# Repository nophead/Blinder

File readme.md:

# Blinder

Tasmota roller blind open / close mechanism

<span></span>

---
## Table of Contents
1. [Parts list](#Parts_list)
1. [Pulley Assembly](#pulley_assembly)
1. [Switch Slide Assembly](#switch_slide_assembly)
1. [Rod Assembly](#rod_assembly)
1. [Retainer Assembly](#retainer_assembly)
1. [Idler Assembly](#idler_assembly)
1. [Base Assembly](#base_assembly)
1. [Motor Assembly](#motor_assembly)
1. [Bracket Assembly](#bracket_assembly)
1. [Blinder PCB Assembly](#blinder_PCB_assembly)
1. [Cover Assembly](#cover_assembly)
1. [Main Assembly](#main_assembly)

<span></span>
[Top](#TOP)

---

## Parts list
| <span style="writing-mode: vertical-rl; text-orientation: mixed;">Switch&nbsp;Slide</span> | <span style="writing-mode: vertical-rl; text-orientation: mixed;">Rod</span> | <span style="writing-mode: vertical-rl; text-orientation: mixed;">Base</span> | <span style="writing-mode: vertical-rl; text-orientation: mixed;">Motor</span> | <span style="writing-mode: vertical-rl; text-orientation: mixed;">Bracket</span> | <span style="writing-mode: vertical-rl; text-orientation: mixed;">Blinder&nbsp;PCB</span> | <span style="writing-mode: vertical-rl; text-orientation: mixed;">Cover</span> | <span style="writing-mode: vertical-rl; text-orientation: mixed;">Main</span> | <span style="writing-mode: vertical-rl; text-orientation: mixed;">TOTALS</span> |  |
|---:|---:|---:|---:|---:|---:|---:|---:|---:|:---|
|  |  |  |  |  |  |  |  | | **Vitamins** |
| &nbsp;&nbsp;.&nbsp; | &nbsp;&nbsp;.&nbsp; | &nbsp;&nbsp;2&nbsp; | &nbsp;&nbsp;.&nbsp; | &nbsp;&nbsp;.&nbsp; | &nbsp;&nbsp;.&nbsp; | &nbsp;&nbsp;.&nbsp; | &nbsp;&nbsp;.&nbsp; |  &nbsp;&nbsp;2&nbsp; | &nbsp;&nbsp; Ball bearing 686ZZ 6mm x 13mm x 5mm |
| &nbsp;&nbsp;.&nbsp; | &nbsp;&nbsp;.&nbsp; | &nbsp;&nbsp;.&nbsp; | &nbsp;&nbsp;.&nbsp; | &nbsp;&nbsp;.&nbsp; | &nbsp;&nbsp;1&nbsp; | &nbsp;&nbsp;.&nbsp; | &nbsp;&nbsp;.&nbsp; |  &nbsp;&nbsp;1&nbsp; | &nbsp;&nbsp; ESP-12F ESP8266 WiFi module |
| &nbsp;&nbsp;2&nbsp; | &nbsp;&nbsp;.&nbsp; | &nbsp;&nbsp;2&nbsp; | &nbsp;&nbsp;.&nbsp; | &nbsp;&nbsp;.&nbsp; | &nbsp;&nbsp;.&nbsp; | &nbsp;&nbsp;.&nbsp; | &nbsp;&nbsp;.&nbsp; |  &nbsp;&nbsp;4&nbsp; | &nbsp;&nbsp; Heatfit insert M2 x 4mm |
| &nbsp;&nbsp;.&nbsp; | &nbsp;&nbsp;.&nbsp; | &nbsp;&nbsp;10&nbsp; | &nbsp;&nbsp;1&nbsp; | &nbsp;&nbsp;.&nbsp; | &nbsp;&nbsp;.&nbsp; | &nbsp;&nbsp;.&nbsp; | &nbsp;&nbsp;.&nbsp; |  &nbsp;&nbsp;11&nbsp; | &nbsp;&nbsp; Heatfit insert M3 x 3mm |
| &nbsp;&nbsp;.&nbsp; | &nbsp;&nbsp;.&nbsp; | &nbsp;&nbsp;.&nbsp; | &nbsp;&nbsp;.&nbsp; | &nbsp;&nbsp;.&nbsp; | &nbsp;&nbsp;1&nbsp; | &nbsp;&nbsp;.&nbsp; | &nbsp;&nbsp;.&nbsp; |  &nbsp;&nbsp;1&nbsp; | &nbsp;&nbsp; JST PH connector 2 way |
| &nbsp;&nbsp;.&nbsp; | &nbsp;&nbsp;.&nbsp; | &nbsp;&nbsp;.&nbsp; | &nbsp;&nbsp;.&nbsp; | &nbsp;&nbsp;.&nbsp; | &nbsp;&nbsp;2&nbsp; | &nbsp;&nbsp;.&nbsp; | &nbsp;&nbsp;.&nbsp; |  &nbsp;&nbsp;2&nbsp; | &nbsp;&nbsp; JST PH connector 3 way |
| &nbsp;&nbsp;.&nbsp; | &nbsp;&nbsp;.&nbsp; | &nbsp;&nbsp;.&nbsp; | &nbsp;&nbsp;.&nbsp; | &nbsp;&nbsp;.&nbsp; | &nbsp;&nbsp;1&nbsp; | &nbsp;&nbsp;.&nbsp; | &nbsp;&nbsp;.&nbsp; |  &nbsp;&nbsp;1&nbsp; | &nbsp;&nbsp; LED 3 mm green |
| &nbsp;&nbsp;.&nbsp; | &nbsp;&nbsp;.&nbsp; | &nbsp;&nbsp;.&nbsp; | &nbsp;&nbsp;.&nbsp; | &nbsp;&nbsp;.&nbsp; | &nbsp;&nbsp;1&nbsp; | &nbsp;&nbsp;.&nbsp; | &nbsp;&nbsp;.&nbsp; |  &nbsp;&nbsp;1&nbsp; | &nbsp;&nbsp; MULTIWATT11 L6203 |
| &nbsp;&nbsp;1&nbsp; | &nbsp;&nbsp;.&nbsp; | &nbsp;&nbsp;1&nbsp; | &nbsp;&nbsp;.&nbsp; | &nbsp;&nbsp;.&nbsp; | &nbsp;&nbsp;.&nbsp; | &nbsp;&nbsp;.&nbsp; | &nbsp;&nbsp;.&nbsp; |  &nbsp;&nbsp;2&nbsp; | &nbsp;&nbsp; Microswitch DM1-00P-110-3 |
| &nbsp;&nbsp;.&nbsp; | &nbsp;&nbsp;.&nbsp; | &nbsp;&nbsp;.&nbsp; | &nbsp;&nbsp;.&nbsp; | &nbsp;&nbsp;.&nbsp; | &nbsp;&nbsp;1&nbsp; | &nbsp;&nbsp;.&nbsp; | &nbsp;&nbsp;.&nbsp; |  &nbsp;&nbsp;1&nbsp; | &nbsp;&nbsp; Molex KK header 2 way |
| &nbsp;&nbsp;.&nbsp; | &nbsp;&nbsp;.&nbsp; | &nbsp;&nbsp;.&nbsp; | &nbsp;&nbsp;.&nbsp; | &nbsp;&nbsp;.&nbsp; | &nbsp;&nbsp;1&nbsp; | &nbsp;&nbsp;.&nbsp; | &nbsp;&nbsp;.&nbsp; |  &nbsp;&nbsp;1&nbsp; | &nbsp;&nbsp; Molex KK housing 2 way |
| &nbsp;&nbsp;.&nbsp; | &nbsp;&nbsp;.&nbsp; | &nbsp;&nbsp;.&nbsp; | &nbsp;&nbsp;.&nbsp; | &nbsp;&nbsp;.&nbsp; | &nbsp;&nbsp;.&nbsp; | &nbsp;&nbsp;1&nbsp; | &nbsp;&nbsp;.&nbsp; |  &nbsp;&nbsp;1&nbsp; | &nbsp;&nbsp; Nut M3 x 2.4mm nyloc |
| &nbsp;&nbsp;.&nbsp; | &nbsp;&nbsp;.&nbsp; | &nbsp;&nbsp;1&nbsp; | &nbsp;&nbsp;.&nbsp; | &nbsp;&nbsp;.&nbsp; | &nbsp;&nbsp;.&nbsp; | &nbsp;&nbsp;.&nbsp; | &nbsp;&nbsp;.&nbsp; |  &nbsp;&nbsp;1&nbsp; | &nbsp;&nbsp; Nut M8 x 6.5mm brass |
| &nbsp;&nbsp;.&nbsp; | &nbsp;&nbsp;.&nbsp; | &nbsp;&nbsp;.&nbsp; | &nbsp;&nbsp;.&nbsp; | &nbsp;&nbsp;.&nbsp; | &nbsp;&nbsp;1&nbsp; | &nbsp;&nbsp;.&nbsp; | &nbsp;&nbsp;.&nbsp; |  &nbsp;&nbsp;1&nbsp; | &nbsp;&nbsp; PCB Blinder |
| &nbsp;&nbsp;.&nbsp; | &nbsp;&nbsp;.&nbsp; | &nbsp;&nbsp;.&nbsp; | &nbsp;&nbsp;.&nbsp; | &nbsp;&nbsp;.&nbsp; | &nbsp;&nbsp;2&nbsp; | &nbsp;&nbsp;.&nbsp; | &nbsp;&nbsp;.&nbsp; |  &nbsp;&nbsp;2&nbsp; | &nbsp;&nbsp; SMD capacitor 0805 100n |
| &nbsp;&nbsp;.&nbsp; | &nbsp;&nbsp;.&nbsp; | &nbsp;&nbsp;.&nbsp; | &nbsp;&nbsp;.&nbsp; | &nbsp;&nbsp;.&nbsp; | &nbsp;&nbsp;2&nbsp; | &nbsp;&nbsp;.&nbsp; | &nbsp;&nbsp;.&nbsp; |  &nbsp;&nbsp;2&nbsp; | &nbsp;&nbsp; SMD capacitor 0805 15n |
| &nbsp;&nbsp;.&nbsp; | &nbsp;&nbsp;.&nbsp; | &nbsp;&nbsp;.&nbsp; | &nbsp;&nbsp;.&nbsp; | &nbsp;&nbsp;.&nbsp; | &nbsp;&nbsp;1&nbsp; | &nbsp;&nbsp;.&nbsp; | &nbsp;&nbsp;.&nbsp; |  &nbsp;&nbsp;1&nbsp; | &nbsp;&nbsp; SMD capacitor 0805 220n |
| &nbsp;&nbsp;.&nbsp; | &nbsp;&nbsp;.&nbsp; | &nbsp;&nbsp;.&nbsp; | &nbsp;&nbsp;.&nbsp; | &nbsp;&nbsp;.&nbsp; | &nbsp;&nbsp;5&nbsp; | &nbsp;&nbsp;.&nbsp; | &nbsp;&nbsp;.&nbsp; |  &nbsp;&nbsp;5&nbsp; | &nbsp;&nbsp; SMD resistor 0805 10K 0.125W |
| &nbsp;&nbsp;.&nbsp; | &nbsp;&nbsp;.&nbsp; | &nbsp;&nbsp;.&nbsp; | &nbsp;&nbsp;.&nbsp; | &nbsp;&nbsp;.&nbsp; | &nbsp;&nbsp;2&nbsp; | &nbsp;&nbsp;.&nbsp; | &nbsp;&nbsp;.&nbsp; |  &nbsp;&nbsp;2&nbsp; | &nbsp;&nbsp; SMD resistor 0805 1K 0.125W |
| &nbsp;&nbsp;.&nbsp; | &nbsp;&nbsp;.&nbsp; | &nbsp;&nbsp;.&nbsp; | &nbsp;&nbsp;.&nbsp; | &nbsp;&nbsp;.&nbsp; | &nbsp;&nbsp;1&nbsp; | &nbsp;&nbsp;.&nbsp; | &nbsp;&nbsp;.&nbsp; |  &nbsp;&nbsp;1&nbsp; | &nbsp;&nbsp; SMD resistor 0805 2K2 0.125W |
| &nbsp;&nbsp;2&nbsp; | &nbsp;&nbsp;.&nbsp; | &nbsp;&nbsp;2&nbsp; | &nbsp;&nbsp;.&nbsp; | &nbsp;&nbsp;.&nbsp; | &nbsp;&nbsp;.&nbsp; | &nbsp;&nbsp;.&nbsp; | &nbsp;&nbsp;.&nbsp; |  &nbsp;&nbsp;4&nbsp; | &nbsp;&nbsp; Screw M2 cap x 10mm |
| &nbsp;&nbsp;.&nbsp; | &nbsp;&nbsp;.&nbsp; | &nbsp;&nbsp;1&nbsp; | &nbsp;&nbsp;.&nbsp; | &nbsp;&nbsp;.&nbsp; | &nbsp;&nbsp;.&nbsp; | &nbsp;&nbsp;.&nbsp; | &nbsp;&nbsp;.&nbsp; |  &nbsp;&nbsp;1&nbsp; | &nbsp;&nbsp; Screw M3 cap x  5mm |
| &nbsp;&nbsp;.&nbsp; | &nbsp;&nbsp;.&nbsp; | &nbsp;&nbsp;.&nbsp; | &nbsp;&nbsp;.&nbsp; | &nbsp;&nbsp;3&nbsp; | &nbsp;&nbsp;.&nbsp; | &nbsp;&nbsp;.&nbsp; | &nbsp;&nbsp;.&nbsp; |  &nbsp;&nbsp;3&nbsp; | &nbsp;&nbsp; Screw M3 cap x  8mm |
| &nbsp;&nbsp;.&nbsp; | &nbsp;&nbsp;.&nbsp; | &nbsp;&nbsp;.&nbsp; | &nbsp;&nbsp;.&nbsp; | &nbsp;&nbsp;.&nbsp; | &nbsp;&nbsp;.&nbsp; | &nbsp;&nbsp;.&nbsp; | &nbsp;&nbsp;4&nbsp; |  &nbsp;&nbsp;4&nbsp; | &nbsp;&nbsp; Screw M3 cs cap x  5mm |
| &nbsp;&nbsp;.&nbsp; | &nbsp;&nbsp;.&nbsp; | &nbsp;&nbsp;.&nbsp; | &nbsp;&nbsp;.&nbsp; | &nbsp;&nbsp;.&nbsp; | &nbsp;&nbsp;.&nbsp; | &nbsp;&nbsp;1&nbsp; | &nbsp;&nbsp;.&nbsp; |  &nbsp;&nbsp;1&nbsp; | &nbsp;&nbsp; Screw M3 cs cap x 12mm |
| &nbsp;&nbsp;.&nbsp; | &nbsp;&nbsp;.&nbsp; | &nbsp;&nbsp;.&nbsp; | &nbsp;&nbsp;6&nbsp; | &nbsp;&nbsp;.&nbsp; | &nbsp;&nbsp;.&nbsp; | &nbsp;&nbsp;.&nbsp; | &nbsp;&nbsp;.&nbsp; |  &nbsp;&nbsp;6&nbsp; | &nbsp;&nbsp; Screw M3 dome x 12mm |
| &nbsp;&nbsp;.&nbsp; | &nbsp;&nbsp;.&nbsp; | &nbsp;&nbsp;2&nbsp; | &nbsp;&nbsp;1&nbsp; | &nbsp;&nbsp;.&nbsp; | &nbsp;&nbsp;.&nbsp; | &nbsp;&nbsp;.&nbsp; | &nbsp;&nbsp;.&nbsp; |  &nbsp;&nbsp;3&nbsp; | &nbsp;&nbsp; Screw M3 grub x  5mm |
| &nbsp;&nbsp;.&nbsp; | &nbsp;&nbsp;.&nbsp; | &nbsp;&nbsp;.&nbsp; | &nbsp;&nbsp;.&nbsp; | &nbsp;&nbsp;3&nbsp; | &nbsp;&nbsp;.&nbsp; | &nbsp;&nbsp;.&nbsp; | &nbsp;&nbsp;.&nbsp; |  &nbsp;&nbsp;3&nbsp; | &nbsp;&nbsp; Screw No8 pan wood x 30mm |
| &nbsp;&nbsp;.&nbsp; | &nbsp;&nbsp;.&nbsp; | &nbsp;&nbsp;.&nbsp; | &nbsp;&nbsp;.&nbsp; | &nbsp;&nbsp;.&nbsp; | &nbsp;&nbsp;2&nbsp; | &nbsp;&nbsp;.&nbsp; | &nbsp;&nbsp;.&nbsp; |  &nbsp;&nbsp;2&nbsp; | &nbsp;&nbsp; Square button 6mm |
| &nbsp;&nbsp;.&nbsp; | &nbsp;&nbsp;1&nbsp; | &nbsp;&nbsp;.&nbsp; | &nbsp;&nbsp;.&nbsp; | &nbsp;&nbsp;.&nbsp; | &nbsp;&nbsp;.&nbsp; | &nbsp;&nbsp;.&nbsp; | &nbsp;&nbsp;.&nbsp; |  &nbsp;&nbsp;1&nbsp; | &nbsp;&nbsp; Threaded rod M8 x 79mm - not shown |
| &nbsp;&nbsp;.&nbsp; | &nbsp;&nbsp;.&nbsp; | &nbsp;&nbsp;.&nbsp; | &nbsp;&nbsp;.&nbsp; | &nbsp;&nbsp;.&nbsp; | &nbsp;&nbsp;1&nbsp; | &nbsp;&nbsp;.&nbsp; | &nbsp;&nbsp;.&nbsp; |  &nbsp;&nbsp;1&nbsp; | &nbsp;&nbsp; Ultra Small 3A buck regulator |
| &nbsp;&nbsp;2&nbsp; | &nbsp;&nbsp;.&nbsp; | &nbsp;&nbsp;2&nbsp; | &nbsp;&nbsp;.&nbsp; | &nbsp;&nbsp;.&nbsp; | &nbsp;&nbsp;.&nbsp; | &nbsp;&nbsp;.&nbsp; | &nbsp;&nbsp;.&nbsp; |  &nbsp;&nbsp;4&nbsp; | &nbsp;&nbsp; Washer  M2 x 5mm x 0.3mm |
| &nbsp;&nbsp;.&nbsp; | &nbsp;&nbsp;.&nbsp; | &nbsp;&nbsp;1&nbsp; | &nbsp;&nbsp;.&nbsp; | &nbsp;&nbsp;3&nbsp; | &nbsp;&nbsp;.&nbsp; | &nbsp;&nbsp;1&nbsp; | &nbsp;&nbsp;.&nbsp; |  &nbsp;&nbsp;5&nbsp; | &nbsp;&nbsp; Washer  M3 x 7mm x 0.5mm |
| &nbsp;&nbsp;.&nbsp; | &nbsp;&nbsp;.&nbsp; | &nbsp;&nbsp;.&nbsp; | &nbsp;&nbsp;.&nbsp; | &nbsp;&nbsp;3&nbsp; | &nbsp;&nbsp;.&nbsp; | &nbsp;&nbsp;.&nbsp; | &nbsp;&nbsp;.&nbsp; |  &nbsp;&nbsp;3&nbsp; | &nbsp;&nbsp; Washer  M5 x 10mm x 1mm |
| &nbsp;&nbsp;.&nbsp; | &nbsp;&nbsp;.&nbsp; | &nbsp;&nbsp;2&nbsp; | &nbsp;&nbsp;.&nbsp; | &nbsp;&nbsp;.&nbsp; | &nbsp;&nbsp;.&nbsp; | &nbsp;&nbsp;.&nbsp; | &nbsp;&nbsp;.&nbsp; |  &nbsp;&nbsp;2&nbsp; | &nbsp;&nbsp; Washer spring M6 x 1.9mm |
| &nbsp;&nbsp;2&nbsp; | &nbsp;&nbsp;.&nbsp; | &nbsp;&nbsp;2&nbsp; | &nbsp;&nbsp;.&nbsp; | &nbsp;&nbsp;.&nbsp; | &nbsp;&nbsp;.&nbsp; | &nbsp;&nbsp;.&nbsp; | &nbsp;&nbsp;.&nbsp; |  &nbsp;&nbsp;4&nbsp; | &nbsp;&nbsp; Washer star M2 x 0.3mm |
| &nbsp;&nbsp;.&nbsp; | &nbsp;&nbsp;.&nbsp; | &nbsp;&nbsp;1&nbsp; | &nbsp;&nbsp;.&nbsp; | &nbsp;&nbsp;.&nbsp; | &nbsp;&nbsp;.&nbsp; | &nbsp;&nbsp;.&nbsp; | &nbsp;&nbsp;.&nbsp; |  &nbsp;&nbsp;1&nbsp; | &nbsp;&nbsp; Washer star M3 x 0.5mm |
| &nbsp;&nbsp;9&nbsp; | &nbsp;&nbsp;1&nbsp; | &nbsp;&nbsp;29&nbsp; | &nbsp;&nbsp;8&nbsp; | &nbsp;&nbsp;12&nbsp; | &nbsp;&nbsp;25&nbsp; | &nbsp;&nbsp;3&nbsp; | &nbsp;&nbsp;4&nbsp; | &nbsp;&nbsp;91&nbsp; | &nbsp;&nbsp;Total vitamins count |
|  |  |  |  |  |  |  |  | | **3D printed parts** |
| &nbsp;&nbsp;.&nbsp; | &nbsp;&nbsp;.&nbsp; | &nbsp;&nbsp;1&nbsp; | &nbsp;&nbsp;.&nbsp; | &nbsp;&nbsp;.&nbsp; | &nbsp;&nbsp;.&nbsp; | &nbsp;&nbsp;.&nbsp; | &nbsp;&nbsp;.&nbsp; |  &nbsp;&nbsp;1&nbsp; | &nbsp;&nbsp;base.stl |
| &nbsp;&nbsp;.&nbsp; | &nbsp;&nbsp;.&nbsp; | &nbsp;&nbsp;.&nbsp; | &nbsp;&nbsp;.&nbsp; | &nbsp;&nbsp;1&nbsp; | &nbsp;&nbsp;.&nbsp; | &nbsp;&nbsp;.&nbsp; | &nbsp;&nbsp;.&nbsp; |  &nbsp;&nbsp;1&nbsp; | &nbsp;&nbsp;bracket.stl |
| &nbsp;&nbsp;.&nbsp; | &nbsp;&nbsp;.&nbsp; | &nbsp;&nbsp;.&nbsp; | &nbsp;&nbsp;.&nbsp; | &nbsp;&nbsp;.&nbsp; | &nbsp;&nbsp;.&nbsp; | &nbsp;&nbsp;1&nbsp; | &nbsp;&nbsp;.&nbsp; |  &nbsp;&nbsp;1&nbsp; | &nbsp;&nbsp;cover.stl |
| &nbsp;&nbsp;.&nbsp; | &nbsp;&nbsp;.&nbsp; | &nbsp;&nbsp;1&nbsp; | &nbsp;&nbsp;.&nbsp; | &nbsp;&nbsp;.&nbsp; | &nbsp;&nbsp;.&nbsp; | &nbsp;&nbsp;.&nbsp; | &nbsp;&nbsp;.&nbsp; |  &nbsp;&nbsp;1&nbsp; | &nbsp;&nbsp;idler.stl |
| &nbsp;&nbsp;.&nbsp; | &nbsp;&nbsp;.&nbsp; | &nbsp;&nbsp;.&nbsp; | &nbsp;&nbsp;1&nbsp; | &nbsp;&nbsp;.&nbsp; | &nbsp;&nbsp;.&nbsp; | &nbsp;&nbsp;.&nbsp; | &nbsp;&nbsp;.&nbsp; |  &nbsp;&nbsp;1&nbsp; | &nbsp;&nbsp;pulley.stl |
| &nbsp;&nbsp;.&nbsp; | &nbsp;&nbsp;.&nbsp; | &nbsp;&nbsp;1&nbsp; | &nbsp;&nbsp;.&nbsp; | &nbsp;&nbsp;.&nbsp; | &nbsp;&nbsp;.&nbsp; | &nbsp;&nbsp;.&nbsp; | &nbsp;&nbsp;.&nbsp; |  &nbsp;&nbsp;1&nbsp; | &nbsp;&nbsp;retainer.stl |
| &nbsp;&nbsp;1&nbsp; | &nbsp;&nbsp;.&nbsp; | &nbsp;&nbsp;.&nbsp; | &nbsp;&nbsp;.&nbsp; | &nbsp;&nbsp;.&nbsp; | &nbsp;&nbsp;.&nbsp; | &nbsp;&nbsp;.&nbsp; | &nbsp;&nbsp;.&nbsp; |  &nbsp;&nbsp;1&nbsp; | &nbsp;&nbsp;switch_slide.stl |
| &nbsp;&nbsp;1&nbsp; | &nbsp;&nbsp;.&nbsp; | &nbsp;&nbsp;3&nbsp; | &nbsp;&nbsp;1&nbsp; | &nbsp;&nbsp;1&nbsp; | &nbsp;&nbsp;.&nbsp; | &nbsp;&nbsp;1&nbsp; | &nbsp;&nbsp;.&nbsp; | &nbsp;&nbsp;7&nbsp; | &nbsp;&nbsp;Total 3D printed parts count |

<span></span>
[Top](#TOP)

---

## Pulley Assembly
### Vitamins
|Qty|Description|
|---:|:----------|
|1| Heatfit insert M3 x 3mm|
|1| Screw M3 grub x  5mm|

### 3D Printed parts

| 1 x pulley.stl |
|---|
|  

### Assembly instructions

1. Fit the heatfit insert
1. Add the grub screw

<span></span>
[Top](#TOP)

---

## Switch Slide Assembly
### Vitamins
|Qty|Description|
|---:|:----------|
|2| Heatfit insert M2 x 4mm|
|1| Microswitch DM1-00P-110-3|
|2| Screw M2 cap x 10mm|
|2| Washer  M2 x 5mm x 0.3mm|
|2| Washer star M2 x 0.3mm|

### 3D Printed parts

| 1 x switch_slide.stl |
|---|
|  

### Assembly instructions

1. Fit the heatfit inserts into the slide.
1. Screw the microswitch to the slide using 10mm M2 cap screws spring washers and plain washers.
1. Solder two wires to the outer pins.

<span></span>
[Top](#TOP)

---

## Rod Assembly
### Vitamins
|Qty|Description|
|---:|:----------|
|1| Threaded rod M8 x 79mm - not shown|

### Assembly instructions

* Turn down the ends of the studding to 5.96mm to fit through the bearings.

<span></span>
[Top](#TOP)

---

## Retainer Assembly
### Vitamins
|Qty|Description|
|---:|:----------|
|1| Heatfit insert M3 x 3mm|
|1| Screw M3 grub x  5mm|

### 3D Printed parts

| 1 x retainer.stl |
|---|
|  

### Assembly instructions

1. Fit the heatfit insert
1. Add the grub screw

<span></span>
[Top](#TOP)

---

## Idler Assembly
### Vitamins
|Qty|Description|
|---:|:----------|
|1| Heatfit insert M3 x 3mm|
|1| Screw M3 grub x  5mm|

### 3D Printed parts

| 1 x idler.stl |
|---|
|  

### Assembly instructions

1. Fit the heatfit insert
1. Add the grub screw

<span></span>
[Top](#TOP)

---

## Base Assembly
### Vitamins
|Qty|Description|
|---:|:----------|
|2| Ball bearing 686ZZ 6mm x 13mm x 5mm|
|2| Heatfit insert M2 x 4mm|
|8| Heatfit insert M3 x 3mm|
|1| Microswitch DM1-00P-110-3|
|1| Nut M8 x 6.5mm brass|
|2| Screw M2 cap x 10mm|
|1| Screw M3 cap x  5mm|
|2| Washer  M2 x 5mm x 0.3mm|
|1| Washer  M3 x 7mm x 0.5mm|
|2| Washer spring M6 x 1.9mm|
|2| Washer star M2 x 0.3mm|
|1| Washer star M3 x 0.5mm|

### 3D Printed parts

| 1 x base.stl |
|---|
|  

### Sub-assemblies

| 1 x idler_assembly | 1 x retainer_assembly | 1 x rod_assembly |
|---|---|---|
|  |  |  

| 1 x switch_slide_assembly |
|---|
|  

### Assembly instructions

1. Fit the 8 M3 inserts, 4 in the ribs, 3 in the base and 1 for the slide
1. Fit two M2 inserts for the microswitch.
1. Place the M8 nut in a central position and screw in the studding.
1. Crush the M8 spring washers with pliers as they are used just as spacers.
1. Fit the bearings and spring washers and secure in place with the pulley and retainer grub screws.
1. Solder two wires to the outer pins of the microswitch and screw it in place.
1. Screw the slide in place in the central position.

<span></span>
[Top](#TOP)

---

## Motor Assembly
### Vitamins
|Qty|Description|
|---:|:----------|
|6| Screw M3 dome x 12mm|

### Sub-assemblies

| 1 x base_assembly | 1 x pulley_assembly |
|---|---|
|  |  

### Assembly instructions

1. Introduce the motor and pulley trapping the ball chain between the pulley and the idler and then screw the motor in place.
1. Solder wires to the motor.
1. Crimp JST plugs to the motors and switch wires. Use the schematic to get the correct pins.

<span></span>
[Top](#TOP)

---

## Bracket Assembly
### Vitamins
|Qty|Description|
|---:|:----------|
|3| Screw M3 cap x  8mm|
|3| Screw No8 pan wood x 30mm|
|3| Washer  M3 x 7mm x 0.5mm|
|3| Washer  M5 x 10mm x 1mm|

### 3D Printed parts

| 1 x bracket.stl |
|---|
|  

### Sub-assemblies

| 1 x motor_assembly |
|---|
|  

### Assembly instructions

1. Screw the bracket to the bottom of the base using 3 8mm M3 cap screws and washers.
1. Screw the bracket to the wall using rawl plugs, No8 screws and M5 washers.
1. Slide it down to tension the ball chain before tightening the screws.
1. Connect the PCB to the switches, motor and 12V power.
1. While controlling the blind with the buttons: adjust the closed position by losening the idler pulley and rotating it on the shaft.
1. Then set the open position by adjustinge the sliding microswitch.

<span></span>
[Top](#TOP)

---

## Blinder PCB Assembly
### Vitamins
|Qty|Description|
|---:|:----------|
|1| ESP-12F ESP8266 WiFi module|
|1| JST PH connector 2 way|
|2| JST PH connector 3 way|
|1| LED 3 mm green|
|1| MULTIWATT11 L6203|
|1| Molex KK header 2 way|
|1| Molex KK housing 2 way|
|1| PCB Blinder|
|2| SMD capacitor 0805 100n|
|2| SMD capacitor 0805 15n|
|1| SMD capacitor 0805 220n|
|5| SMD resistor 0805 10K 0.125W|
|2| SMD resistor 0805 1K 0.125W|
|1| SMD resistor 0805 2K2 0.125W|
|2| Square button 6mm|
|1| Ultra Small 3A buck regulator|

### Assembly instructions

1. Use a paste mask to apply solder paste to the SMD pads.
1. Place the SMD parts on the solder.
1. Use an oven or hotplate to reflow the solder.
1. Alternatively the SMD parts and pads are big enough to hand solder.
1. Hand solder the through hole connectors, switches, LED and L6203. The LED's flange should align with the board edge.
1. Solder wires into the tink_buck converter, mount it on a double sided sticky pad and solder the wires to the PCB.
1. Crop all the leads short on the underside of the board.

<span></span>
[Top](#TOP)

---

## Cover Assembly
### Vitamins
|Qty|Description|
|---:|:----------|
|1| Nut M3 x 2.4mm nyloc|
|1| Screw M3 cs cap x 12mm|
|1| Washer  M3 x 7mm x 0.5mm|

### 3D Printed parts

| 1 x cover.stl |
|---|
|  

### Sub-assemblies

| 1 x blinder_PCB_assembly |
|---|
|  

### Assembly instructions

1. Cut away the support material under the PCB spacer boss.
1. Place the PCB into the large guide and level with the top of the small guide and then slide forwards.
1. Secure with the screw, washer and nut.

<span></span>
[Top](#TOP)

---

## Main Assembly
### Vitamins
|Qty|Description|
|---:|:----------|
|4| Screw M3 cs cap x  5mm|

### Sub-assemblies

| 1 x bracket_assembly | 1 x cover_assembly |
|---|---|
|  |  

### Assembly instructions

1. Place the 12V power cable in the slot in the base.
1. Place the cover assembly over the base and secure with four screws.

<span></span>
[Top](#TOP)

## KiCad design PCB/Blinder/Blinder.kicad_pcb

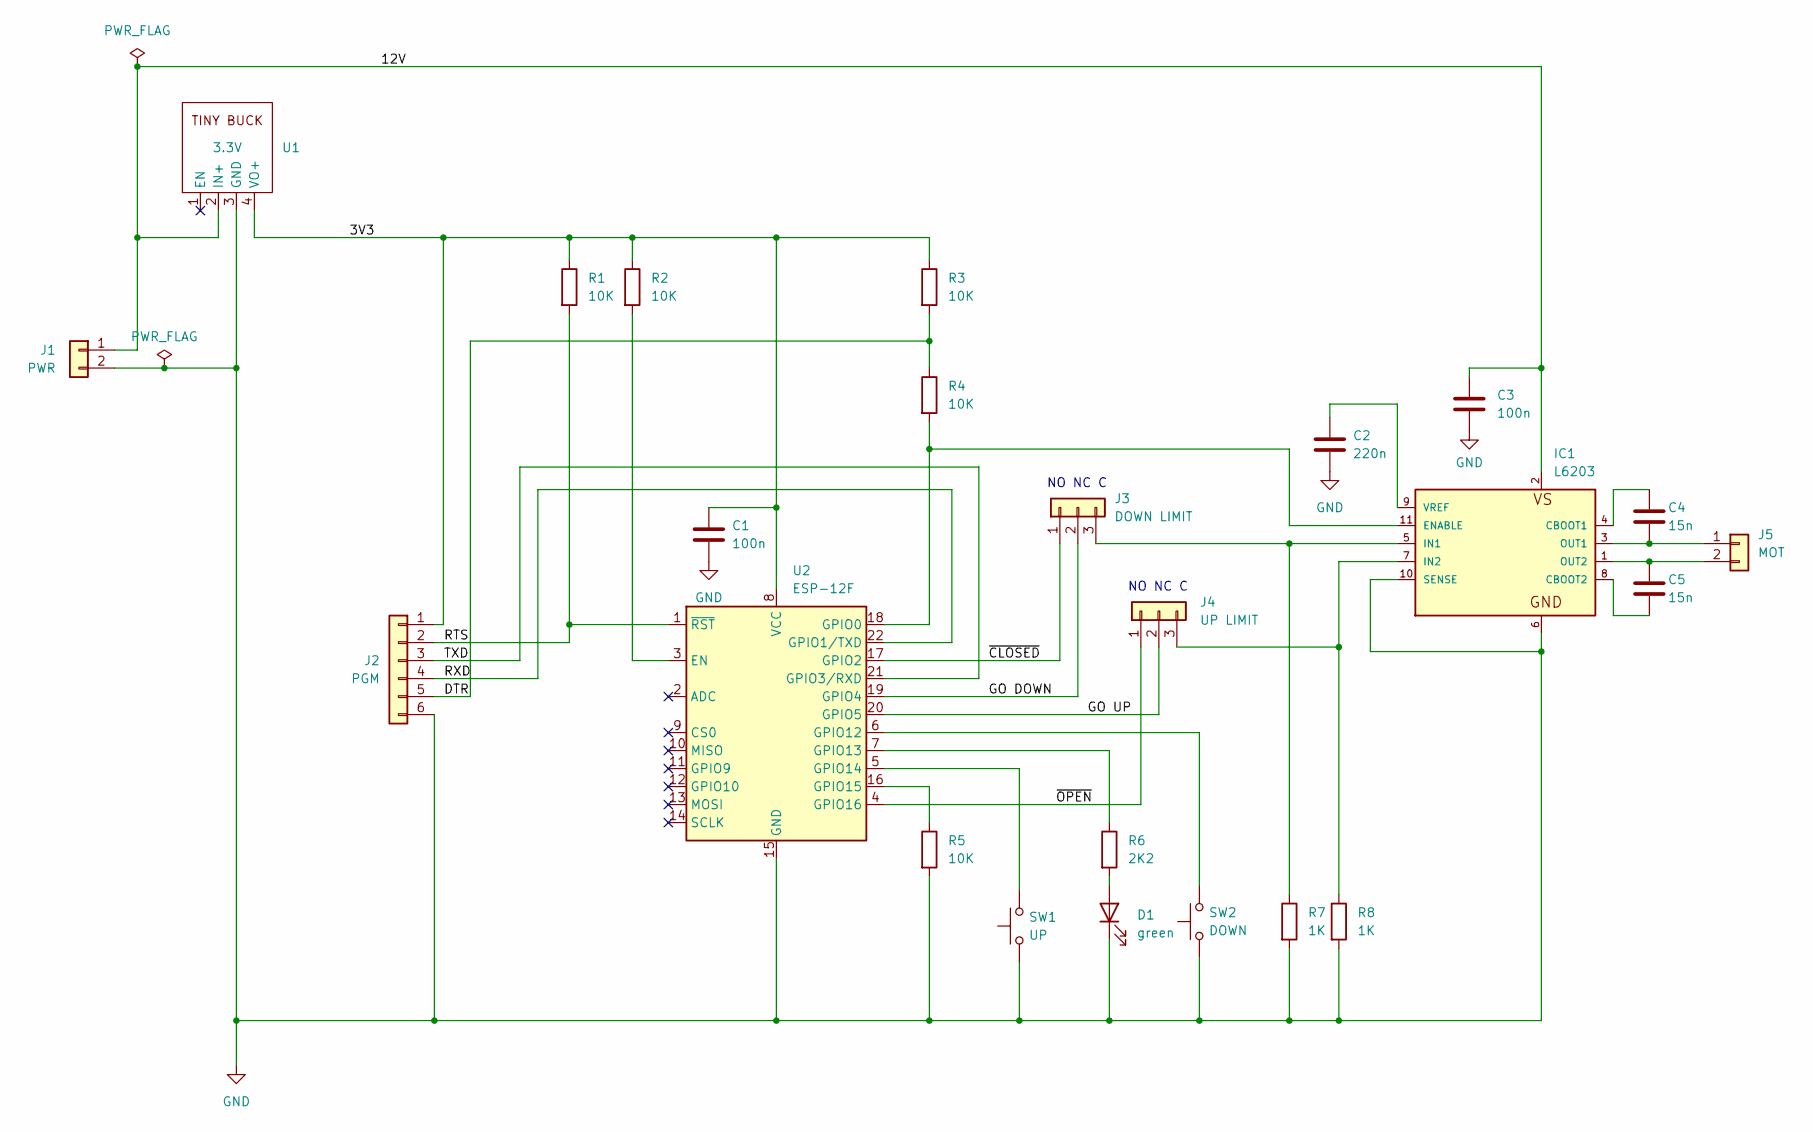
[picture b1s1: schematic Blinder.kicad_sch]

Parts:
C1, C3: 100n; C_0805_2012Metric_Pad1.18x1.45mm_HandSolder
C2: 220n; C_0805_2012Metric_Pad1.18x1.45mm_HandSolder
C4, C5: 15n; C_0805_2012Metric_Pad1.18x1.45mm_HandSolder
D1: green; LED_D3.0mm_Horizontal_O1.27mm_Z2.0mm
IC1: L6203; MULTIWATT-11; MPN L6203
J1: PWR; Molex_KK-254_AE-6410-02A_1x02_P2.54mm_Vertical
J2: PGM; PinHeader_1x06_P2.54mm_Vertical
J3: DOWN LIMIT; JST_PH_B3B-PH-K_1x03_P2.00mm_Vertical
J4: UP LIMIT; JST_PH_B3B-PH-K_1x03_P2.00mm_Vertical
J5: MOT; JST_PH_B2B-PH-K_1x02_P2.00mm_Vertical
R1, R2, R3, R4, R5: 10K; R_0805_2012Metric_Pad1.20x1.40mm_HandSolder
R6: 2K2; R_0805_2012Metric_Pad1.20x1.40mm_HandSolder
R7, R8: 1K; R_0805_2012Metric_Pad1.20x1.40mm_HandSolder
SW1: UP; SW_Tactile_SPST_Angled_PTS645Vx39-2LFS
SW2: DOWN; SW_Tactile_SPST_Angled_PTS645Vx39-2LFS
U1: 3.3V; TinyBuck
U2: ESP-12F; ESP-12E

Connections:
/3V3: C1.1, J2.1, R1.1, R2.1, R3.1, U1.4 (VO+), U2.8 (VCC)
/12V: C3.1, IC1.2, J1.1, U1.2 (IN+)
/DTR: J2.5, R3.2, R4.1
/GO DOWN: J3.2, U2.19 (GPIO4)
/GO UP: J4.2, U2.20 (GPIO5)
/RTS: J2.2, R1.2, U2.1 (~RST)
/RXD: J2.4, U2.22 (GPIO1/TXD)
/TXD: J2.3, U2.21 (GPIO3/RXD)
/~CLOSED: J3.1, U2.17 (GPIO2)
/~OPEN: J4.1, U2.4 (GPIO16)
GND: C1.2, C2.2, C3.2, D1.1 (K), IC1.6, IC1.10 (SENSE), J1.2, J2.6, R5.2, R7.2, R8.2, SW1.1, SW2.1, U1.3 (GND), U2.15 (GND)
unnamed: D1.2 (A), R6.2
unnamed: C4.1, IC1.4 (CBOOT1)
unnamed: C5.2, IC1.8 (CBOOT2)
unnamed: IC1.11 (ENABLE), R4.2, U2.18 (GPIO0)
unnamed: IC1.5 (IN1), J3.3, R7.1
unnamed: IC1.7 (IN2), J4.3, R8.1
unnamed: C4.2, IC1.3 (OUT1), J5.1
unnamed: C5.1, IC1.1 (OUT2), J5.2
unnamed: C2.1, IC1.9 (VREF)
unnamed: R2.2, U2.3 (EN)
unnamed: SW2.2, U2.6 (GPIO12)
unnamed: R6.1, U2.7 (GPIO13)
unnamed: SW1.2, U2.5 (GPIO14)
unnamed: R5.1, U2.16 (GPIO15)

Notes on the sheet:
NO NC C

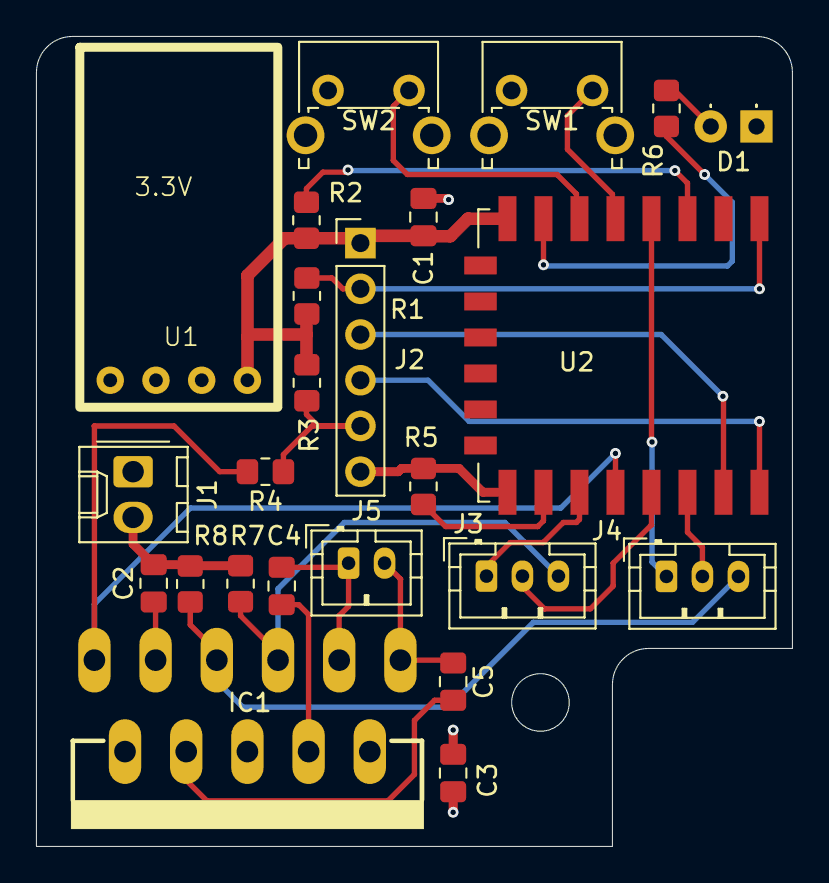
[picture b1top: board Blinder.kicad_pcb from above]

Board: 4 copper layers, 42.0 x 45.0 mm, 24 parts (0 on the bottom side), 25 nets.

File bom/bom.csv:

'Ball bearing 686ZZ 6mm x 13mm x 5mm',  2
'Heatfit insert M3 x 3mm', 11
'Heatfit insert M2 x 4mm',  4
'JST PH connector 2 way',  1
'JST PH connector 3 way',  2
'LED 3 mm green',  1
'Microswitch DM1-00P-110-3',  2
'Molex KK header 2 way',  1
'Molex KK housing 2 way',  1
'MULTIWATT11 L6203',  1
'Nut M3 x 2.4mm nyloc',  1
'Nut M8 x 6.5mm brass',  1
'PCB Blinder',  1
'ESP-12F ESP8266 WiFi module',  1
'Ultra Small 3A buck regulator',  1
'Screw M2 cap x 10mm',  4
'Screw M3 cap x  5mm',  1
'Screw M3 cap x  8mm',  3
'Screw M3 cs cap x 12mm',  1
'Screw M3 cs cap x  5mm',  4
'Screw M3 dome x 12mm',  6
'Screw M3 grub x  5mm',  3
'Screw No8 pan wood x 30mm',  3
'SMD capacitor 0805 100n',  2
'SMD capacitor 0805 15n',  2
'SMD capacitor 0805 220n',  1
'SMD resistor 0805 10K 0.125W',  5
'SMD resistor 0805 1K 0.125W',  2
'SMD resistor 0805 2K2 0.125W',  1
'Washer spring M6 x 1.9mm',  2
'Square button 6mm',  2
'Washer star M2 x 0.3mm',  4
'Washer star M3 x 0.5mm',  1
'Threaded rod M8 x 79mm - not shown',  1
'Washer  M2 x 5mm x 0.3mm',  4
'Washer  M3 x 7mm x 0.5mm',  5
'Washer  M5 x 10mm x 1mm',  3

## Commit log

2023-12-04 First commit.
2023-12-04 Fixed parts list width.
2023-12-29 Fixed copywrite dates.
